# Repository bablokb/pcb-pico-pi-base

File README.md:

pcb-pico-pi-base
================

This projects provides two adapter-boards to run Pi-hats with a Pico.

The "pico-zero-base":

and the "pico-pi-base":

The boards support (besides digital IO) I2C, I2S and SPI.

Supported Hats
--------------

The following hats were successfully tested:

  - Scroll pHat HD
  - Touch pHat
  - 4-Letter pHat
  - LED-Shim
  - Button-Shim
  - Pirate-Audio Speaker-Hat
  - Pirate-Audio Shim
  - Adafruit Speaker Bonnet
  - Display-Otron-Hat
  - InkyImpression  5.7"
  - Inky wHAT (black and white version)
  - Waveshare 4 inch RPi LCD (A)
  - I2C-Multiplexer-pHat

See the [examples page](examples/Readme.md) for details.

Hardware
--------

KiCad design-files are in `pico-zero-base.kicad` and in `pico-pi-base.kicad`
respectively. Ready to upload production files for JLCPCB are in `production_files`.

Except for I2C-pullups (and VSYS-diode on pico-pi-base) the adapter-boards
only map the pins of the Pico to pins of the Pi. The current versions
support I2C, SPI0, SPI1, I2S.

Schematic, layout and 3D-rendered images for pico-zero-base:

Schematic, layout and 3D-rendered images for pico-pi-base:

Software
--------

Since you cannot run Linux-software on the Pico, you need to check if there is a
Pico-driver available for your hats or adapt existing Pi drivers to the Pico. Since
many hats have python-drivers, this is not too difficult. Most hats only use
I2C and/or SPI anyhow.

In the directory `lib` you will find CircuitPython drivers for the supported
hats, unless there is a ready to use driver available.

The directory `examples` contains example programs.

The software currently assumes that you use special CircuitPython-builds
that do the pin mapping (see the directory `circuitpython`).
If not, you have to manually look up the [mapping](mapping.ods).

Porting to MicroPython from CircuitPython should be very simple, since
CircuitPython is only a fork of MicroPython and all the drivers use only
I2C, SPI and digital-IO.

License
-------

[![CC BY-SA 4.0][cc-by-sa-shield]][cc-by-sa]

This work is licensed under a
[Creative Commons Attribution-ShareAlike 4.0 International
License][cc-by-sa].

[![CC BY-SA 4.0][cc-by-sa-image]][cc-by-sa]

[cc-by-sa]: http://creativecommons.org/licenses/by-sa/4.0/
[cc-by-sa-image]: https://licensebuttons.net/l/by-sa/4.0/88x31.png
[cc-by-sa-shield]:
https://img.shields.io/badge/License-CC%20BY--SA%204.0-lightgrey.svg

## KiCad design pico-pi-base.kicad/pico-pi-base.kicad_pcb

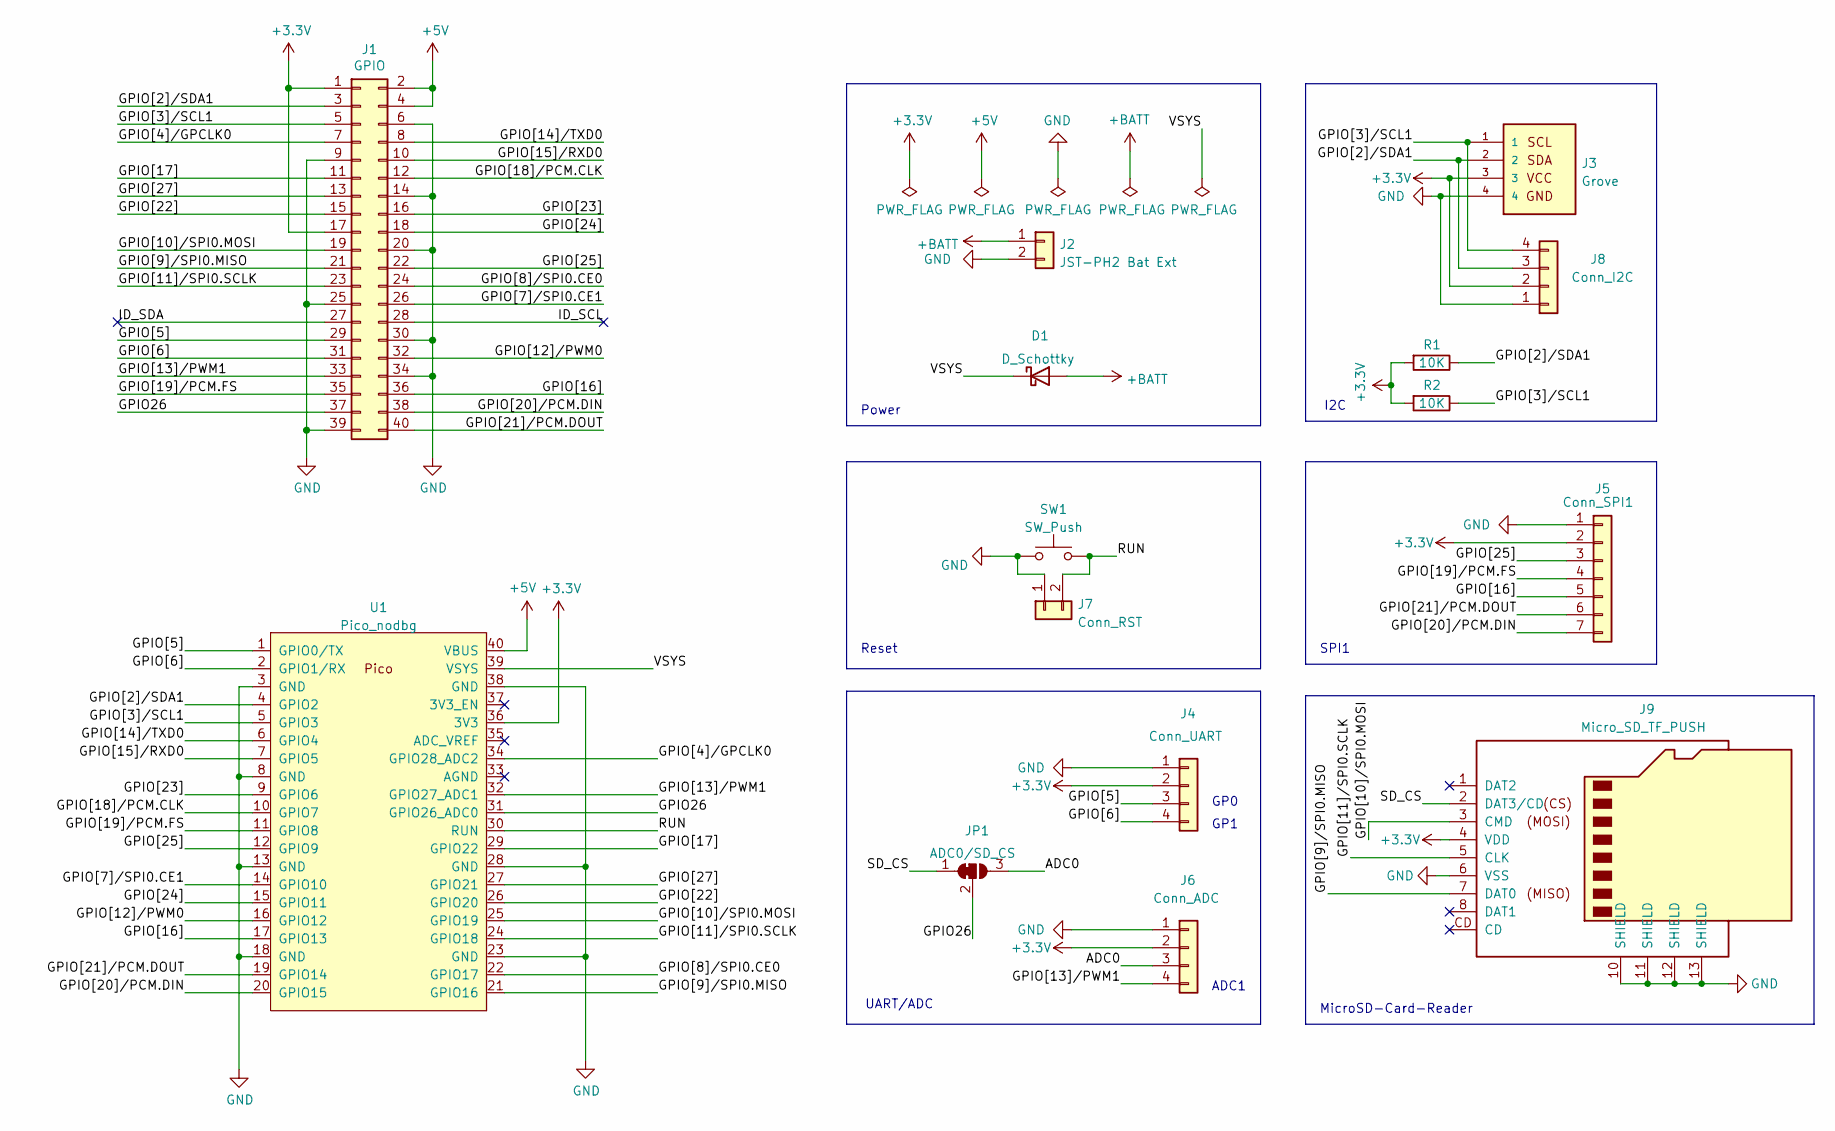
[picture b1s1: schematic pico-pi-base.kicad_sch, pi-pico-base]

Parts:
D1: D_Schottky; D_SMA; LCSC C2480
J1: GPIO; PinHeader_2x20_P2.54mm_Vertical
J2: JST-PH2 Bat Ext; JST_PH_S2B-PH-SM4-TB_1x02-1MP_P2.00mm_Horizontal
J3: Grove; grove_horizontal
J4: Conn_UART; PinSocket_1x04_P2.54mm_Horizontal
J5: Conn_SPI1; PinSocket_1x07_P2.54mm_Horizontal
J6: Conn_ADC; PinSocket_1x04_P2.54mm_Horizontal
J7: Conn_RST; PinHeader_1x02_P2.54mm_Horizontal
J8: Conn_I2C; PinHeader_1x04_P2.54mm_Horizontal
J9: Micro_SD_TF_PUSH; TF-Push; LCSC C393941
JP1: ADC0/SD_CS; SolderJumper-3_P1.3mm_Bridged12_Pad1.0x1.5mm
R1, R2: 10K; R_0603_1608Metric; LCSC C25804
SW1: SW_Push; Microtaster_Horizontal
U1: Pico_nodbg; RPi_Pico_SMD_TH_nodbg

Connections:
+3.3V: J1.1, J1.17, J3.3, J4.2, J5.2, J6.2, J8.2, J9.4 (VDD), R1.2, R2.2, U1.36 (3V3)
+5V: J1.2, J1.4, U1.40 (VBUS)
+BATT: D1.2 (A), J2.1
/ADC0: J6.3, JP1.3 (B)
/GPIO26: J1.37, JP1.2 (C), U1.31 (GPIO26_ADC0)
/GPIO[2]/SDA1: J1.3, J3.2, J8.3, R1.1, U1.4 (GPIO2)
/GPIO[3]/SCL1: J1.5, J3.1, J8.4, R2.1, U1.5 (GPIO3)
/GPIO[4]/GPCLK0: J1.7, U1.34 (GPIO28_ADC2)
/GPIO[5]: J1.29, J4.3, U1.1 (GPIO0/TX)
/GPIO[6]: J1.31, J4.4, U1.2 (GPIO1/RX)
/GPIO[7]/SPI0.CE1: J1.26, U1.14 (GPIO10)
/GPIO[8]/SPI0.CE0: J1.24, U1.22 (GPIO17)
/GPIO[9]/SPI0.MISO: J1.21, J9.7 (DAT0), U1.21 (GPIO16)
/GPIO[10]/SPI0.MOSI: J1.19, J9.3 (CMD), U1.25 (GPIO19)
/GPIO[11]/SPI0.SCLK: J1.23, J9.5 (CLK), U1.24 (GPIO18)
/GPIO[12]/PWM0: J1.32, U1.16 (GPIO12)
/GPIO[13]/PWM1: J1.33, J6.4, U1.32 (GPIO27_ADC1)
/GPIO[14]/TXD0: J1.8, U1.6 (GPIO4)
/GPIO[15]/RXD0: J1.10, U1.7 (GPIO5)
/GPIO[16]: J1.36, J5.5, U1.17 (GPIO13)
/GPIO[17]: J1.11, U1.29 (GPIO22)
/GPIO[18]/PCM.CLK: J1.12, U1.10 (GPIO7)
/GPIO[19]/PCM.FS: J1.35, J5.4, U1.11 (GPIO8)
/GPIO[20]/PCM.DIN: J1.38, J5.7, U1.20 (GPIO15)
/GPIO[21]/PCM.DOUT: J1.40, J5.6, U1.19 (GPIO14)
/GPIO[22]: J1.15, U1.26 (GPIO20)
/GPIO[23]: J1.16, U1.9 (GPIO6)
/GPIO[24]: J1.18, U1.15 (GPIO11)
/GPIO[25]: J1.22, J5.3, U1.12 (GPIO9)
/GPIO[27]: J1.13, U1.27 (GPIO21)
/ID_SCL: J1.28
/ID_SDA: J1.27
/RUN: J7.2, SW1.2, U1.30 (RUN)
/SD_CS: J9.2 (DAT3/CD), JP1.1 (A)
/VSYS: D1.1 (K), U1.39 (VSYS)
GND: J1.6, J1.9, J1.14, J1.20, J1.25, J1.30, J1.34, J1.39, J2.2, J3.4, J4.1, J5.1, J6.1, J7.1, J8.1, J9.6 (VSS), J9.10 (SHIELD), J9.11 (SHIELD), J9.12 (SHIELD), J9.13 (SHIELD), SW1.1, U1.3 (GND), U1.8 (GND), U1.13 (GND), U1.18 (GND), U1.23 (GND), U1.28 (GND), U1.38 (GND)

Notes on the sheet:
Reset
GP0
Power
GP1
MicroSD-Card-Reader
SPI1
UART/ADC
I2C
ADC1

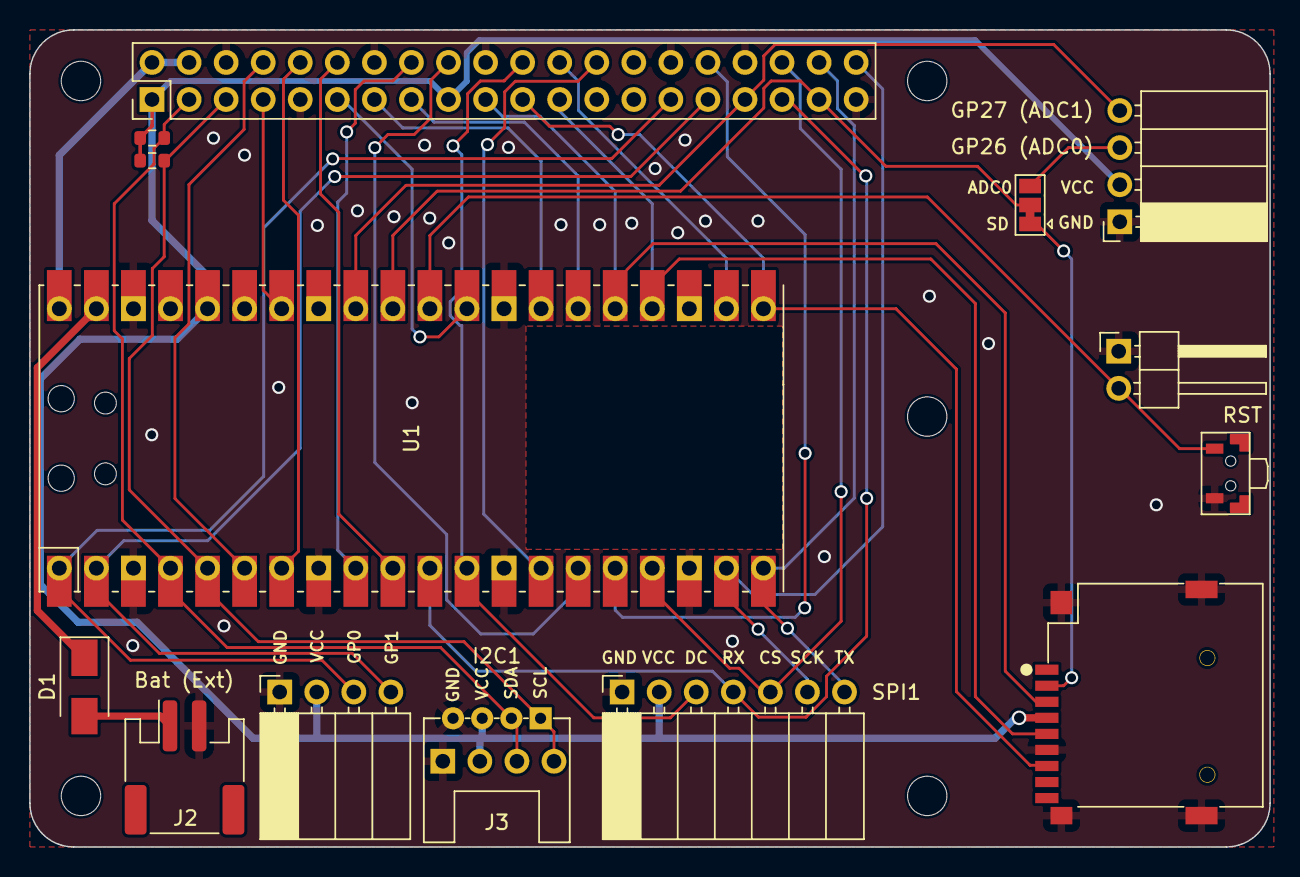
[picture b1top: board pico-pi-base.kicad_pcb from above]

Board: 2 copper layers, 85.0 x 56.0 mm, 20 parts (1 on the bottom side), 34 nets.

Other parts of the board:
MH1, MH1#2, MH2, MH3, MH4: MountingHole_2.7mm_M2.5

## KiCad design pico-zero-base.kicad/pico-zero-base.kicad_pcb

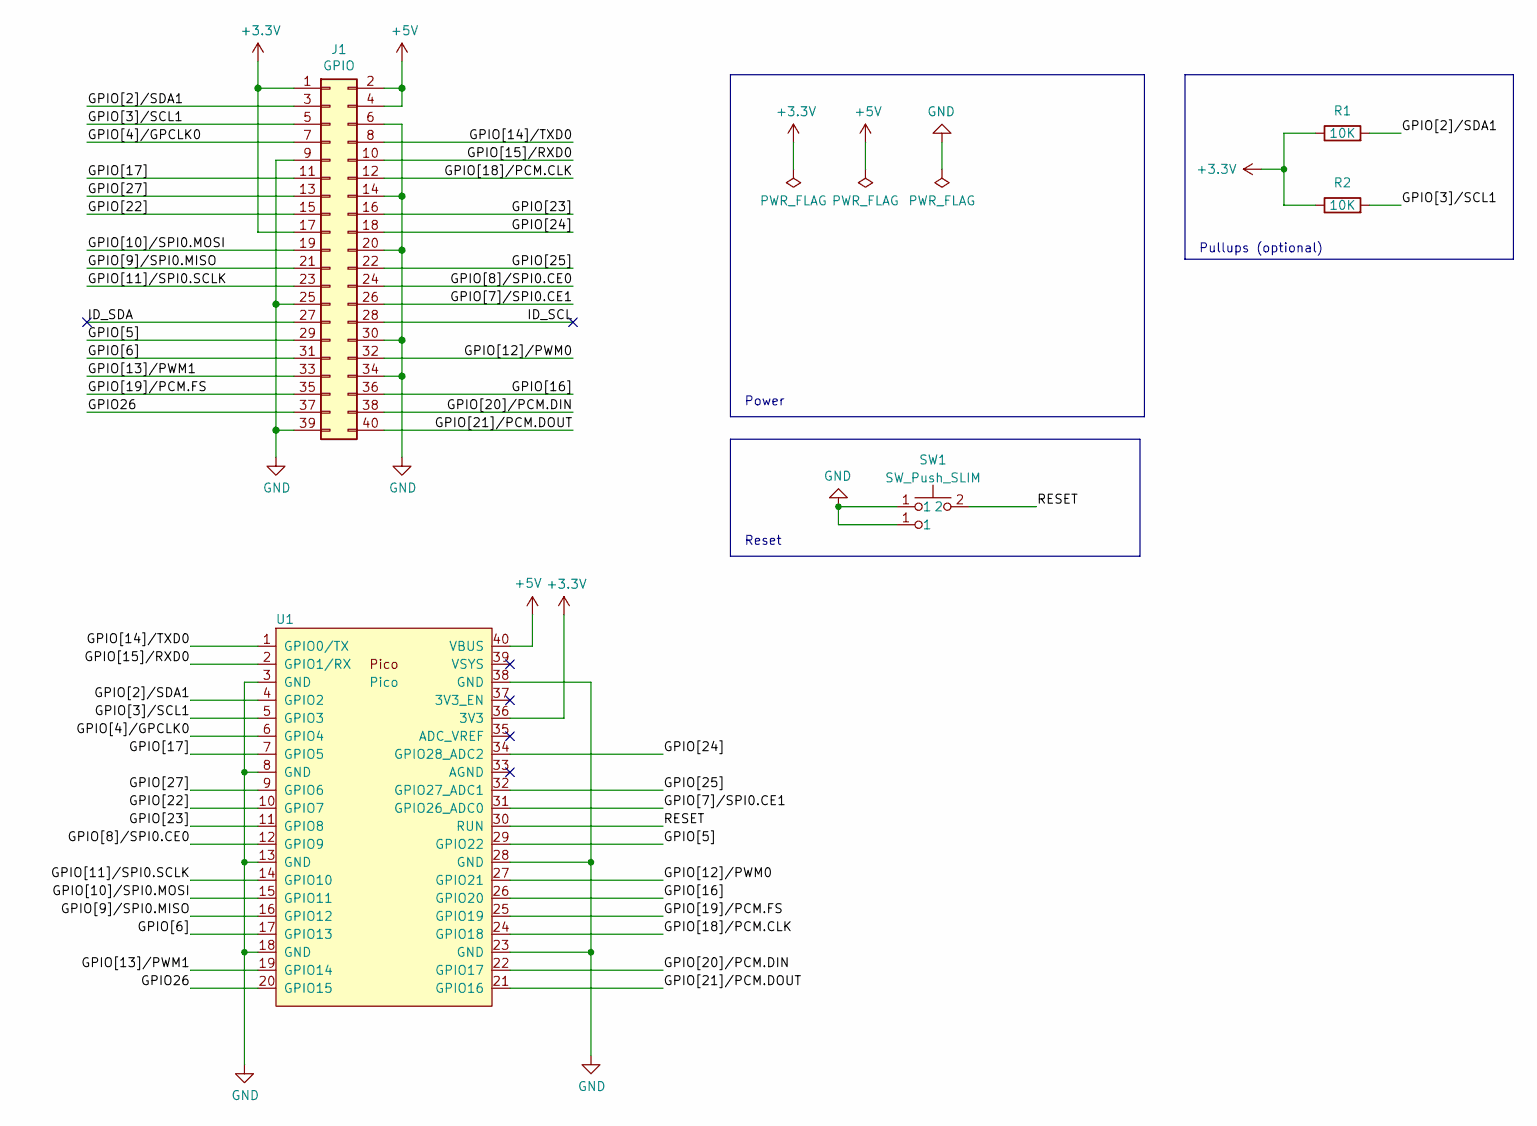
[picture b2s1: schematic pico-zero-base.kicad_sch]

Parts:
J1: GPIO; PinHeader_2x20_P2.54mm_Vertical
R1, R2: 10K; R_1206_3216Metric_Pad1.30x1.75mm_HandSolder; LCSC C17902
SW1: SW_Push_SLIM; SW_PUSH_SLIM_1x4
U1: Pico; RPi_Pico_SMD_TH_nodbg

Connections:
+3.3V: J1.1, J1.17, R1.1, R2.1, U1.36 (3V3)
+5V: J1.2, J1.4, U1.40 (VBUS)
/GPIO26: J1.37, U1.20 (GPIO15)
/GPIO[2]/SDA1: J1.3, R1.2, U1.4 (GPIO2)
/GPIO[3]/SCL1: J1.5, R2.2, U1.5 (GPIO3)
/GPIO[4]/GPCLK0: J1.7, U1.6 (GPIO4)
/GPIO[5]: J1.29, U1.29 (GPIO22)
/GPIO[6]: J1.31, U1.17 (GPIO13)
/GPIO[7]/SPI0.CE1: J1.26, U1.31 (GPIO26_ADC0)
/GPIO[8]/SPI0.CE0: J1.24, U1.12 (GPIO9)
/GPIO[9]/SPI0.MISO: J1.21, U1.16 (GPIO12)
/GPIO[10]/SPI0.MOSI: J1.19, U1.15 (GPIO11)
/GPIO[11]/SPI0.SCLK: J1.23, U1.14 (GPIO10)
/GPIO[12]/PWM0: J1.32, U1.27 (GPIO21)
/GPIO[13]/PWM1: J1.33, U1.19 (GPIO14)
/GPIO[14]/TXD0: J1.8, U1.1 (GPIO0/TX)
/GPIO[15]/RXD0: J1.10, U1.2 (GPIO1/RX)
/GPIO[16]: J1.36, U1.26 (GPIO20)
/GPIO[17]: J1.11, U1.7 (GPIO5)
/GPIO[18]/PCM.CLK: J1.12, U1.24 (GPIO18)
/GPIO[19]/PCM.FS: J1.35, U1.25 (GPIO19)
/GPIO[20]/PCM.DIN: J1.38, U1.22 (GPIO17)
/GPIO[21]/PCM.DOUT: J1.40, U1.21 (GPIO16)
/GPIO[22]: J1.15, U1.10 (GPIO7)
/GPIO[23]: J1.16, U1.11 (GPIO8)
/GPIO[24]: J1.18, U1.34 (GPIO28_ADC2)
/GPIO[25]: J1.22, U1.32 (GPIO27_ADC1)
/GPIO[27]: J1.13, U1.9 (GPIO6)
/ID_SCL: J1.28
/ID_SDA: J1.27
/RESET: SW1.2, U1.30 (RUN)
GND: J1.6, J1.9, J1.14, J1.20, J1.25, J1.30, J1.34, J1.39, SW1.1, U1.3 (GND), U1.8 (GND), U1.13 (GND), U1.18 (GND), U1.23 (GND), U1.28 (GND), U1.38 (GND)

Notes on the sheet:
Pullups (optional)
Power
Reset

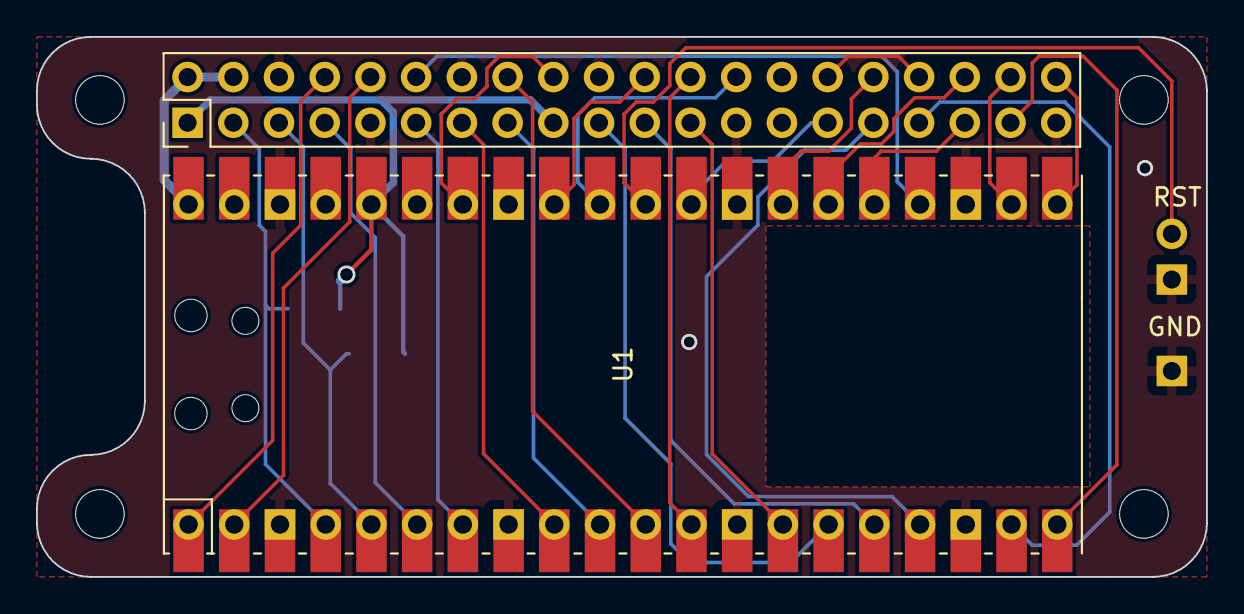
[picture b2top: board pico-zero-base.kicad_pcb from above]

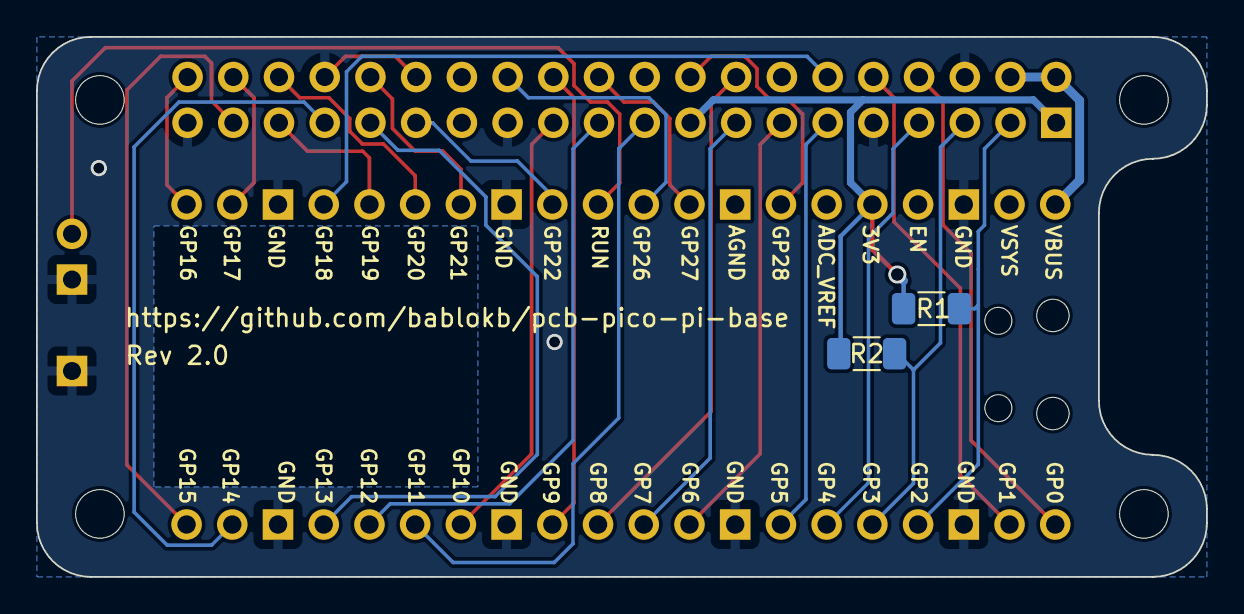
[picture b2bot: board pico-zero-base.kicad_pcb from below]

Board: 2 copper layers, 65.0 x 30.0 mm, 9 parts (2 on the bottom side), 30 nets.

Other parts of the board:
MH1, MH2, MH3, MH4: MountingHole_2.7mm_M2.5

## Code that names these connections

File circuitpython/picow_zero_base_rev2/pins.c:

#include "shared-bindings/board/__init__.h"

STATIC const mp_rom_map_elem_t board_module_globals_table[] = {
    CIRCUITPYTHON_BOARD_DICT_STANDARD_ITEMS

    { MP_ROM_QSTR(MP_QSTR_GP0), MP_ROM_PTR(&pin_GPIO0) },
    { MP_ROM_QSTR(MP_QSTR_GP1), MP_ROM_PTR(&pin_GPIO1) },
    { MP_ROM_QSTR(MP_QSTR_GP2), MP_ROM_PTR(&pin_GPIO2) },
    { MP_ROM_QSTR(MP_QSTR_GP3), MP_ROM_PTR(&pin_GPIO3) },
    { MP_ROM_QSTR(MP_QSTR_GP4), MP_ROM_PTR(&pin_GPIO4) },
    { MP_ROM_QSTR(MP_QSTR_GP5), MP_ROM_PTR(&pin_GPIO5) },
    { MP_ROM_QSTR(MP_QSTR_GP6), MP_ROM_PTR(&pin_GPIO6) },
    { MP_ROM_QSTR(MP_QSTR_GP7), MP_ROM_PTR(&pin_GPIO7) },
    { MP_ROM_QSTR(MP_QSTR_GP8), MP_ROM_PTR(&pin_GPIO8) },
    { MP_ROM_QSTR(MP_QSTR_GP9), MP_ROM_PTR(&pin_GPIO9) },
    { MP_ROM_QSTR(MP_QSTR_GP10), MP_ROM_PTR(&pin_GPIO10) },
    { MP_ROM_QSTR(MP_QSTR_GP11), MP_ROM_PTR(&pin_GPIO11) },
    { MP_ROM_QSTR(MP_QSTR_GP12), MP_ROM_PTR(&pin_GPIO12) },
    { MP_ROM_QSTR(MP_QSTR_GP13), MP_ROM_PTR(&pin_GPIO13) },
    { MP_ROM_QSTR(MP_QSTR_GP14), MP_ROM_PTR(&pin_GPIO14) },
    { MP_ROM_QSTR(MP_QSTR_GP15), MP_ROM_PTR(&pin_GPIO15) },
    { MP_ROM_QSTR(MP_QSTR_GP16), MP_ROM_PTR(&pin_GPIO16) },
    { MP_ROM_QSTR(MP_QSTR_GP17), MP_ROM_PTR(&pin_GPIO17) },
    { MP_ROM_QSTR(MP_QSTR_GP18), MP_ROM_PTR(&pin_GPIO18) },
    { MP_ROM_QSTR(MP_QSTR_GP19), MP_ROM_PTR(&pin_GPIO19) },
    { MP_ROM_QSTR(MP_QSTR_GP20), MP_ROM_PTR(&pin_GPIO20) },
    { MP_ROM_QSTR(MP_QSTR_GP21), MP_ROM_PTR(&pin_GPIO21) },
    { MP_ROM_QSTR(MP_QSTR_GP22), MP_ROM_PTR(&pin_GPIO22) },
    { MP_ROM_QSTR(MP_QSTR_GP26), MP_ROM_PTR(&pin_GPIO26) },
    { MP_ROM_QSTR(MP_QSTR_GP27), MP_ROM_PTR(&pin_GPIO27) },
    { MP_ROM_QSTR(MP_QSTR_GP28), MP_ROM_PTR(&pin_GPIO28) },

    { MP_ROM_QSTR(MP_QSTR_GPIO14), MP_ROM_PTR(&pin_GPIO0) },
    { MP_ROM_QSTR(MP_QSTR_TX), MP_ROM_PTR(&pin_GPIO0) },

    { MP_ROM_QSTR(MP_QSTR_GPIO15), MP_ROM_PTR(&pin_GPIO1) },
    { MP_ROM_QSTR(MP_QSTR_RX), MP_ROM_PTR(&pin_GPIO1) },

    { MP_ROM_QSTR(MP_QSTR_GPIO2), MP_ROM_PTR(&pin_GPIO2) },
    { MP_ROM_QSTR(MP_QSTR_SDA), MP_ROM_PTR(&pin_GPIO2) },

    { MP_ROM_QSTR(MP_QSTR_GPIO3), MP_ROM_PTR(&pin_GPIO3) },
    { MP_ROM_QSTR(MP_QSTR_SCL), MP_ROM_PTR(&pin_GPIO3) },

    { MP_ROM_QSTR(MP_QSTR_GPIO4), MP_ROM_PTR(&pin_GPIO4) },

    { MP_ROM_QSTR(MP_QSTR_GPIO17), MP_ROM_PTR(&pin_GPIO5) },

    { MP_ROM_QSTR(MP_QSTR_GPIO27), MP_ROM_PTR(&pin_GPIO6) },

    { MP_ROM_QSTR(MP_QSTR_GPIO22), MP_ROM_PTR(&pin_GPIO7) },

    { MP_ROM_QSTR(MP_QSTR_GPIO23), MP_ROM_PTR(&pin_GPIO8) },

    { MP_ROM_QSTR(MP_QSTR_GPIO8), MP_ROM_PTR(&pin_GPIO9) },
    { MP_ROM_QSTR(MP_QSTR_CE0), MP_ROM_PTR(&pin_GPIO9) },

    { MP_ROM_QSTR(MP_QSTR_GPIO11), MP_ROM_PTR(&pin_GPIO10) },
    { MP_ROM_QSTR(MP_QSTR_SCLK), MP_ROM_PTR(&pin_GPIO10) },

    { MP_ROM_QSTR(MP_QSTR_GPIO10), MP_ROM_PTR(&pin_GPIO11) },
    { MP_ROM_QSTR(MP_QSTR_MOSI), MP_ROM_PTR(&pin_GPIO11) },

    { MP_ROM_QSTR(MP_QSTR_GPIO9), MP_ROM_PTR(&pin_GPIO12) },
    { MP_ROM_QSTR(MP_QSTR_MISO), MP_ROM_PTR(&pin_GPIO12) },

    { MP_ROM_QSTR(MP_QSTR_GPIO6), MP_ROM_PTR(&pin_GPIO13) },

    { MP_ROM_QSTR(MP_QSTR_GPIO13), MP_ROM_PTR(&pin_GPIO14) },

    { MP_ROM_QSTR(MP_QSTR_GPIO26), MP_ROM_PTR(&pin_GPIO15) },

    { MP_ROM_QSTR(MP_QSTR_GPIO21), MP_ROM_PTR(&pin_GPIO16) },

    { MP_ROM_QSTR(MP_QSTR_GPIO20), MP_ROM_PTR(&pin_GPIO17) },

    { MP_ROM_QSTR(MP_QSTR_GPIO18), MP_ROM_PTR(&pin_GPIO18) },

    { MP_ROM_QSTR(MP_QSTR_GPIO19), MP_ROM_PTR(&pin_GPIO19) },

    { MP_ROM_QSTR(MP_QSTR_GPIO16), MP_ROM_PTR(&pin_GPIO20) },

    { MP_ROM_QSTR(MP_QSTR_GPIO12), MP_ROM_PTR(&pin_GPIO21) },

    { MP_ROM_QSTR(MP_QSTR_GPIO5), MP_ROM_PTR(&pin_GPIO22) },

    { MP_ROM_QSTR(MP_QSTR_GPIO7),  MP_ROM_PTR(&pin_GPIO26) },
    { MP_ROM_QSTR(MP_QSTR_CE1),    MP_ROM_PTR(&pin_GPIO26) },

    { MP_ROM_QSTR(MP_QSTR_GPIO25), MP_ROM_PTR(&pin_GPIO27) },

    { MP_ROM_QSTR(MP_QSTR_GPIO24), MP_ROM_PTR(&pin_GPIO28) },

    { MP_ROM_QSTR(MP_QSTR_SMPS_MODE), MP_ROM_PTR(&pin_CYW1) },

    { MP_ROM_QSTR(MP_QSTR_LED), MP_ROM_PTR(&pin_CYW0) },

    { MP_ROM_QSTR(MP_QSTR_VBUS_SENSE), MP_ROM_PTR(&pin_CYW2) },

    { MP_ROM_QSTR(MP_QSTR_GP26_A0), MP_ROM_PTR(&pin_GPIO26) },
    { MP_ROM_QSTR(MP_QSTR_A0), MP_ROM_PTR(&pin_GPIO26) },

    { MP_ROM_QSTR(MP_QSTR_GP27_A1), MP_ROM_PTR(&pin_GPIO27) },
    { MP_ROM_QSTR(MP_QSTR_A1), MP_ROM_PTR(&pin_GPIO27) },

    { MP_ROM_QSTR(MP_QSTR_GP28_A2), MP_ROM_PTR(&pin_GPIO28) },
    { MP_ROM_QSTR(MP_QSTR_A2), MP_ROM_PTR(&pin_GPIO28) },

    { MP_ROM_QSTR(MP_QSTR_VOLTAGE_MONITOR), MP_ROM_PTR(&pin_GPIO29) },
    { MP_ROM_QSTR(MP_QSTR_A3), MP_ROM_PTR(&pin_GPIO29) },

    { MP_ROM_QSTR(MP_QSTR_I2C), MP_ROM_PTR(&board_i2c_obj) },
    { MP_ROM_QSTR(MP_QSTR_UART), MP_ROM_PTR(&board_uart_obj) },
};
MP_DEFINE_CONST_DICT(board_module_globals, board_module_globals_table);

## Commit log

2023-04-01 initial commit (Rev 1)
2023-04-06 Pico Zero Base Rev 1
2023-04-06 Added reset-button
2023-04-06 use pin-header instead of socket Rev 1.1
2023-04-06 increase 3V3 trace width to 0.4
2023-04-07 add optional pullups Rev 1.2
2023-04-11 pico-pi-base Rev 1.2
2023-04-21 be more specific about excluded lib-directories
2023-04-22 added support for Touch-pHat
2023-04-27 added content
2023-04-27 Rev 2.0: swapped pins to support I2S
2023-04-28 Rev 2.1: add MicroSD-BFF
2023-04-28 added source-url
2023-04-29 added 4-Letter-pHat and LED-Shim
2023-05-02 added info about Pirate-Audio-Hat
2023-05-04 added driver and examples for Display-Otron-Hat
2023-05-04 added files
2023-05-04 added method 'on(...)'
2023-05-04 added information
2023-05-04 removed note about I2S not available on pico-zero-base
2023-05-06 pico-zero-base: Rev 2.0
2023-05-06 don't use board.SPI()
2023-05-06 renamed wifi.py -> ip_test.py
2023-05-08 pico-pi-base: Rev. 2.2
2023-05-08 updated with images
2023-05-12 document InkyImpression
2023-05-18 document rev1+rev2 pinouts
2023-05-19 support Button-Shim
2023-05-19 CircuitPython board-definitions for pico-zero-base rev2 (for Pico)
2023-05-20 add support for Adafruit Speaker-Bonnet
2023-05-21 removed executable flag
2023-05-21 added Audio DAC shim and example for Pirate-Audio
2023-05-26 simplify by using loop=True
2023-05-26 added note about Pirate-Hats using MISO
2023-05-27 updated to rev2
2023-05-27 CircuitPython board-definitions for pico-pi-base-w rev2 (for Pico-W)
2023-05-27 minor wording change
2023-07-05 added example for I2C-Multiplexer pHat from 8086.net
2023-07-17 added pinout for Adafruit-RFM9x-radio-bonnet
2023-09-14 added example for Adafruit's LoRa-bonnet
2023-09-15 minor tweaks in rfm9x processing
2023-09-15 optimized UI-code
2023-09-18 added snr/rssi to output
2023-09-18 added support for pico-zero-base-w Rev2
2024-01-12 added support for Pimoroni Inky wHat
2024-01-12 set tx_power to maximum in the example
2024-01-12 updated READMEs for Inky wHat
2024-02-13 fixed info about I2S
2024-03-28 renamed directories for consistency
2024-03-28 changed board name for consistency
2024-03-28 add support for Waveshare ESP32S3-Pico
2024-03-28 updated mapping info for zero
2024-03-29 added board-files for ESP32S3 on zero-base-rev1
2024-04-19 added support for Waveshare 4inch_RPi_LCD_(A)
2024-06-03 added link to repo from dglaude
2024-07-22 minor code cleanup
2024-07-22 added support for Pimoroni's Inky-pHat
2024-07-22 hardcode width/height in driver
2024-07-23 add seconds_per_frame=6
